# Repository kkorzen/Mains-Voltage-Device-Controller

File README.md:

## Contents

- [Introduction](#introduction)
- [Electronics schematics + PCB Layout](#electronics-schematics--pcb-layout)
- [Arduino Code](#arduino-code)
- [Application](#application)

## Introduction

This project was under development during the first semester of Master's Studies at Warsaw University of Technology (Poland) as a final project for Industrial Communication Protocols. Using the UART adaptation of RS-232, a simple controller was created. Its main goal was to make it possible to control a flow of mains current to the load devices. The device contains of two relays for bi-stable control and one triac for more "analogue" control (e.g., a lightbulb dimmer). The heart is an Arduino Nano board.

To make it a complete device with an "easy-to-use" logic, a simple desktop application was created that allows the user to change the states of two included relays and adjust the output voltage of a triac via a slider.

## Electronics schematics + PCB Layout

Electronics schematic was made with KiCad. The whole schematic was divided into six sections to clarify different modules of the device.

### Power section

This section contains only a single screw terminal for mains voltage connection. Through this terminal, the mains voltage/current are later delivered to the load devices. 

Disclaimer:\
"Zasilanie 230 VAC" means "230 VAC power supply". 

### Zero-cross detection

This section, one of the most important, is responsible for detecting the moment when a mains voltage's sine wave is crossing its zero point. As shown in the image given below, as the sine wave has a non-zero value, the optocouple is pulling the ZCD voltage to ground, but at the time the sine has a value of **zero** the ZCD voltage is pulled high through the 10k resistor $R_3$.

### Bistable relay

Both of these relays are used to control the power delivery for any load that works with mains voltage. Moreover, it is possible to control any device that takes the mains voltage as the binary control input.

For additional protection, a BJT transistor was used as an element responsible for activating the relay's coil.

### Triac dimmer

When the dimmer module is enabled by setting the _DIMMER_EN_ voltage to HIGH, the optotriac diode is connected to ground, completing the circuit. Then, for a specific period of time, the _DIMM_TRIAC_ voltage is set to HIGH, activating the optotriac. This behavior results in the main triac activating for a specified time, resulting in delivering a specified amount of power to the connected load.

#### <u>IMPORTANT</u>

Because the project utilizes a triac, only a resistive load is recommended to avoid the appearance of so-called **tail current**.

### Control logic

A simple schematic for an Arduino with a drawn pinout. Nothing special, to be honest :sweat_smile:. A button was added to enable and disable dimmer, although the MCU can be reprogrammed to utilize this switch differently.

### PCB Layout

Both sides of board were utilized, but most of the traces are located on the front. The were two main goals while designed such layout:
1. Relatively compact size
2. Visible separation of mains AC volatage from the control +5 volts. There is no physical gap between them, but the PCB was designed in such way that control voltage occupies one side of the PCB and the main voltage - the other side.

The layout can be viewed using one of the free PCB design software, for example KiCad.

## Arduino code

Code written for an ATmega328P microcontroller (on an Arduino board) is not anything sophisticated, although it utilizes an ISR for accurate zero-cross detection of mains voltage sine wave.

For communication, it uses a USB protocol (and a USB <> UART transcoder)  which, by transmitting and receiving characters, can be controlled by an external desktop app.

In the source code, there is also a potentiometer pinout definition ```#define POT A0```, which was used for manual testing of the dimmer code + circuit combination before the development of the app. It was mounted only on the prototype board (manually soldered on the perfboard) and is not included in the final project. 

The range of a triac activation delay (```triac_delay```) was selected with a so-called trial-and-error method. Values exceeding the range of 300–9000 have been marked as causing the dimmer to be unstable. Feel free to experiment with this range, however please be careful.

## Application

It's a simple application - nothing revolutionary, although it was a pretty good micro challenge, which surely gave me an insight into making an app communicating with an external device.

When the app is opened, firstly, an appropriate COM port has to be selected using the combo box and then, by clicking the "Connect" button, the app will (or not if an invalid COM was selected) connect itself with a device, thus enabling the control section (right-hand side of the app's screen). 

By clicking the "ON" and "OFF" buttons, you can change the state of both relays, respectively. The section below, called "Sine Wave Control", is responsible, as the name suggests, for adjusting the power delivered to the dimmer and its load (read the important warning in the [Triac dimmer](#triac-dimmer) section). 

If the connection is lost or the app is closed without disconnecting, all the relays are turned off and the dimmer power is set to 0%.

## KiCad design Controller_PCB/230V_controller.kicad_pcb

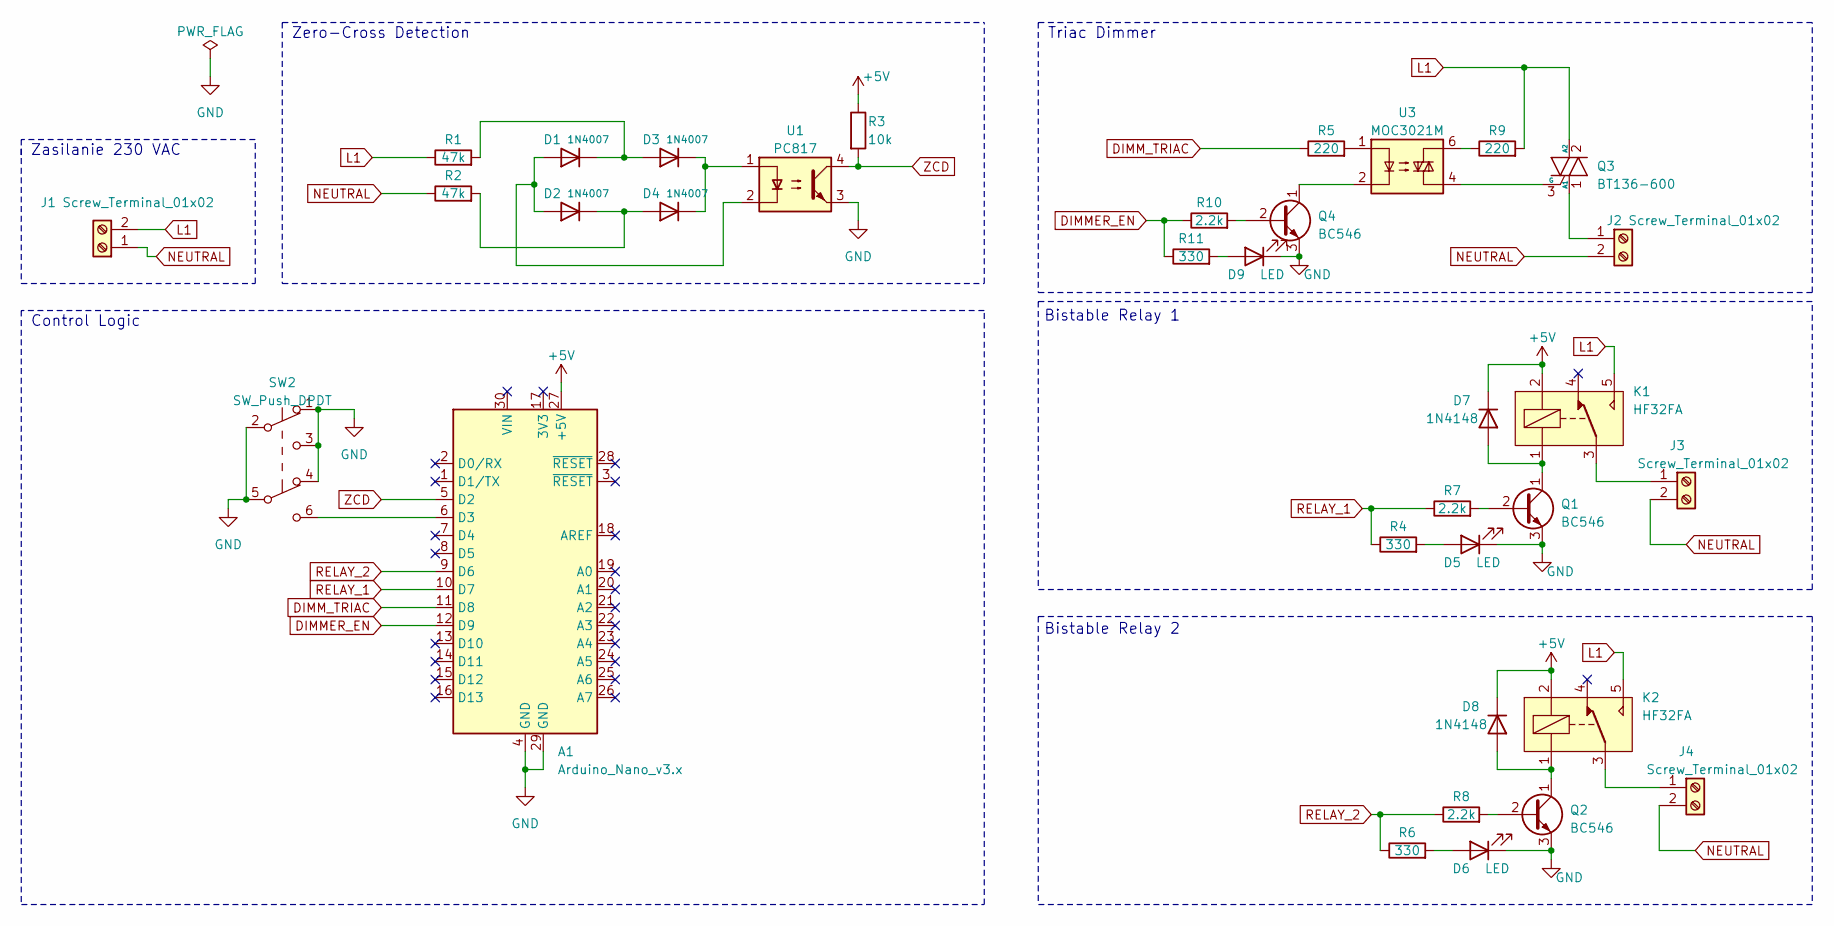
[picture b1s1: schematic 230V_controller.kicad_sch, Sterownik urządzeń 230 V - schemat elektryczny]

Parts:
A1: Arduino_Nano_v3.x; Arduino_Nano
D1, D2, D3, D4: 1N4007; D_DO-41_SOD81_P10.16mm_Horizontal
D5, D6, D9: LED; LED_D3.0mm
D7, D8: 1N4148; D_DO-35_SOD27_P7.62mm_Horizontal
J1, J2, J3, J4: Screw_Terminal_01x02; TerminalBlock_Phoenix_MKDS-1,5-2_1x02_P5.00mm_Horizontal
K1, K2: HF32FA; HF32FA_Type1_FormC
Q1, Q2, Q4: BC546; TO-92_Inline_Wide
Q3: BT136-600; TO-220-3_Vertical
R1, R2: 47k; R_Axial_DIN0207_L6.3mm_D2.5mm_P10.16mm_Horizontal
R3: 10k; R_Axial_DIN0207_L6.3mm_D2.5mm_P10.16mm_Horizontal
R4, R6, R11: 330; R_Axial_DIN0207_L6.3mm_D2.5mm_P10.16mm_Horizontal
R5, R9: 220; R_Axial_DIN0207_L6.3mm_D2.5mm_P10.16mm_Horizontal
R7, R8, R10: 2.2k; R_Axial_DIN0207_L6.3mm_D2.5mm_P10.16mm_Horizontal
SW2: SW_Push_DPDT; SW_Push_2P2T_Toggle_CK_PVA2xxH1xxxxxxV2
U1: PC817; DIP-4_W7.62mm
U3: MOC3021M; DIP-6_W7.62mm

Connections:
+5V: A1.27 (+5V), D7.1 (K), D8.1 (K), K1.2, K2.2, R3.1
DIMMER_EN: A1.12 (D9), R10.1, R11.1
DIMM_TRIAC: A1.11 (D8), R5.1
GND: A1.4 (GND), A1.29 (GND), D5.1 (K), D6.1 (K), D9.1 (K), Q1.3 (E), Q2.3 (E), Q4.3 (E), SW2.1 (A), SW2.2 (B), SW2.3 (C), SW2.4 (A), SW2.5 (B), U1.3
L1: J1.2, K1.5, K2.5, Q3.2 (A2), R1.1, R9.2
NEUTRAL: J1.1, J2.2, J3.2, J4.2, R2.1
unnamed: D1.2 (A), D2.2 (A), U1.2
unnamed: D1.1 (K), D3.2 (A), R1.2
unnamed: D2.1 (K), D4.2 (A), R2.2
unnamed: D3.1 (K), D4.1 (K), U1.1
unnamed: D5.2 (A), R4.2
unnamed: D6.2 (A), R6.2
unnamed: D7.2 (A), K1.1, Q1.1 (C)
unnamed: D8.2 (A), K2.1, Q2.1 (C)
unnamed: D9.2 (A), R11.2
unnamed: J2.1, Q3.1 (A1)
unnamed: J3.1, K1.3
unnamed: J4.1, K2.3
unnamed: Q1.2 (B), R7.2
unnamed: Q2.2 (B), R8.2
unnamed: Q3.3 (G), U3.4
unnamed: Q4.2 (B), R10.2
unnamed: Q4.1 (C), U3.2
unnamed: R5.2, U3.1
unnamed: R9.1, U3.6
RELAY_1: A1.10 (D7), R4.1, R7.1
RELAY_2: A1.9 (D6), R6.1, R8.1
ZCD: A1.5 (D2), R3.2, U1.4

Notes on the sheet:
Control Logic
Zasilanie 230 VAC
Bistable Relay 1
Triac Dimmer
Bistable Relay 2
Zero-Cross Detection

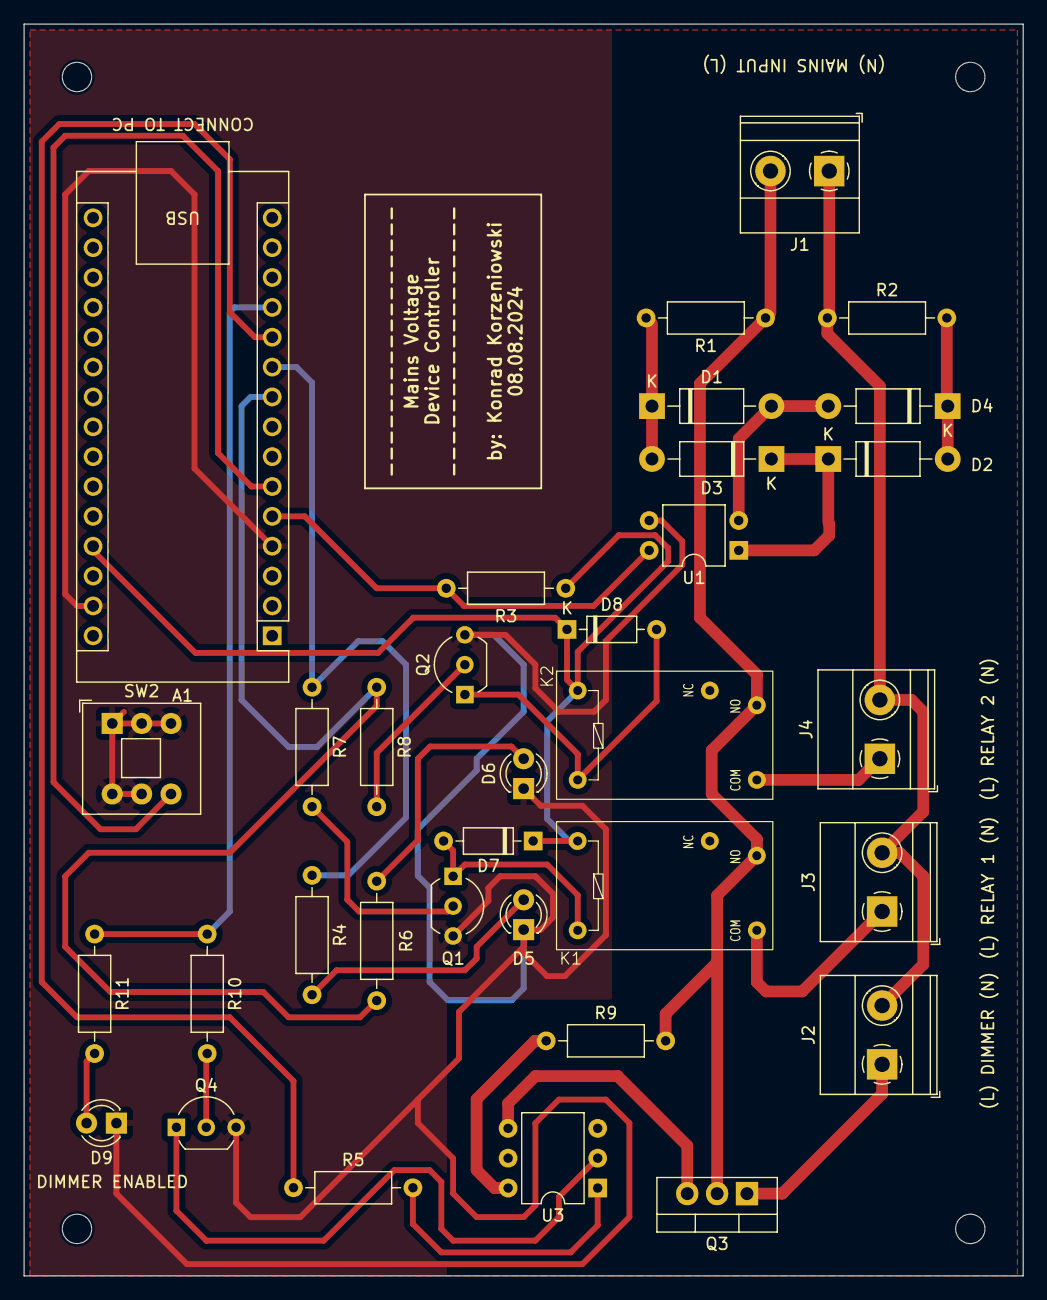
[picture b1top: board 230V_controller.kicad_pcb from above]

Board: 2 copper layers, 85.0 x 106.5 mm, 34 parts (0 on the bottom side), 28 nets.

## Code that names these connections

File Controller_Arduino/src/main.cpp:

#include <Arduino.h>

#define POT A0
#define ZCD 2
#define OPTO_TRIAC_BUTTON 3
#define OPTO_TRIAC_ENABLE 9
#define OPTO_TRIAC 8
#define RELAY_1 6
#define RELAY_2 7

short pot_reading = 0;
int triac_delay = 9000;
int reading = 0, prev_reading = 0;
volatile bool is_zcd = false;

char c;
char d1;
String dataIn;

int counter = 0;
uint64_t remtime = 0;

void ISR_Dimm();

void setup() {
  // pinMode(ZCD, INPUT);
  pinMode(OPTO_TRIAC_BUTTON, INPUT_PULLUP);
  pinMode(OPTO_TRIAC, OUTPUT);
  pinMode(OPTO_TRIAC_ENABLE, OUTPUT);
  pinMode(RELAY_1, OUTPUT);
  pinMode(RELAY_2, OUTPUT);
  attachInterrupt(digitalPinToInterrupt(ZCD), ISR_Dimm, RISING);

  Serial.begin(115200);
  digitalWrite(RELAY_1, 0);
  digitalWrite(RELAY_2, 0);
}

void loop() {
  // pot_reading = analogRead(POT);
  // triac_delay = map(pot_reading, 0, 1023, 300, 9000);

  digitalWrite(OPTO_TRIAC_ENABLE, digitalRead(OPTO_TRIAC_BUTTON));

  while (Serial.available() > 0) {
    c = Serial.read();
    if (c == '\n') {
      Serial.println(dataIn);
      break;
    } else {
      dataIn += c;
    }
  }

  if (c == '\n') {
    switch (dataIn.charAt(0)) {
      case 'L':
        dataIn = dataIn.substring(1);
        triac_delay = dataIn.toInt();
        triac_delay = map(triac_delay, 300, 9000, 9000, 300);
        break;
      case 'A':
        digitalWrite(RELAY_2, 1);
        break;
      case 'a':
        digitalWrite(RELAY_2, 0);
        break;
      case 'B':
        digitalWrite(RELAY_1, 1);
        break;
      case 'b':
        digitalWrite(RELAY_1, 0);
        break;
      default:
        break;
    }
    c = 0;
    dataIn = "";
  }

  if (is_zcd == true) {
    delayMicroseconds(triac_delay);
    digitalWrite(OPTO_TRIAC, HIGH);
    delayMicroseconds(10);
    digitalWrite(OPTO_TRIAC, LOW);
    is_zcd = false;
    
  }
}

void ISR_Dimm() {
  is_zcd = true;
}

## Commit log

2024-07-04 Initial Commit
    Added:
    - Project MCU Code (Arduino)
    - Project Electrical Schematic
    - Project Control App
2024-07-06 A little schematic update Nothing to worry about :) (I just don't remeber what I've changed)
2024-07-06 Update README.md Whole README file has been writte, All the necessary images have added in a separate directory
2024-08-08 Added PCB Design
2024-08-08 Upload new README imgs
2024-08-09 PCB Update Rotated the signature
2024-08-09 General update 1. Updated PCB traces (little fix to make them more straight), 2. Updated Gerber Files, 3. Removed GND zone in the Mains Voltage part of PCB to make it more secure, 4. Updated README.m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
2024-08-09 Added gerberfiles.zip
2024-09-03 Updated source code
